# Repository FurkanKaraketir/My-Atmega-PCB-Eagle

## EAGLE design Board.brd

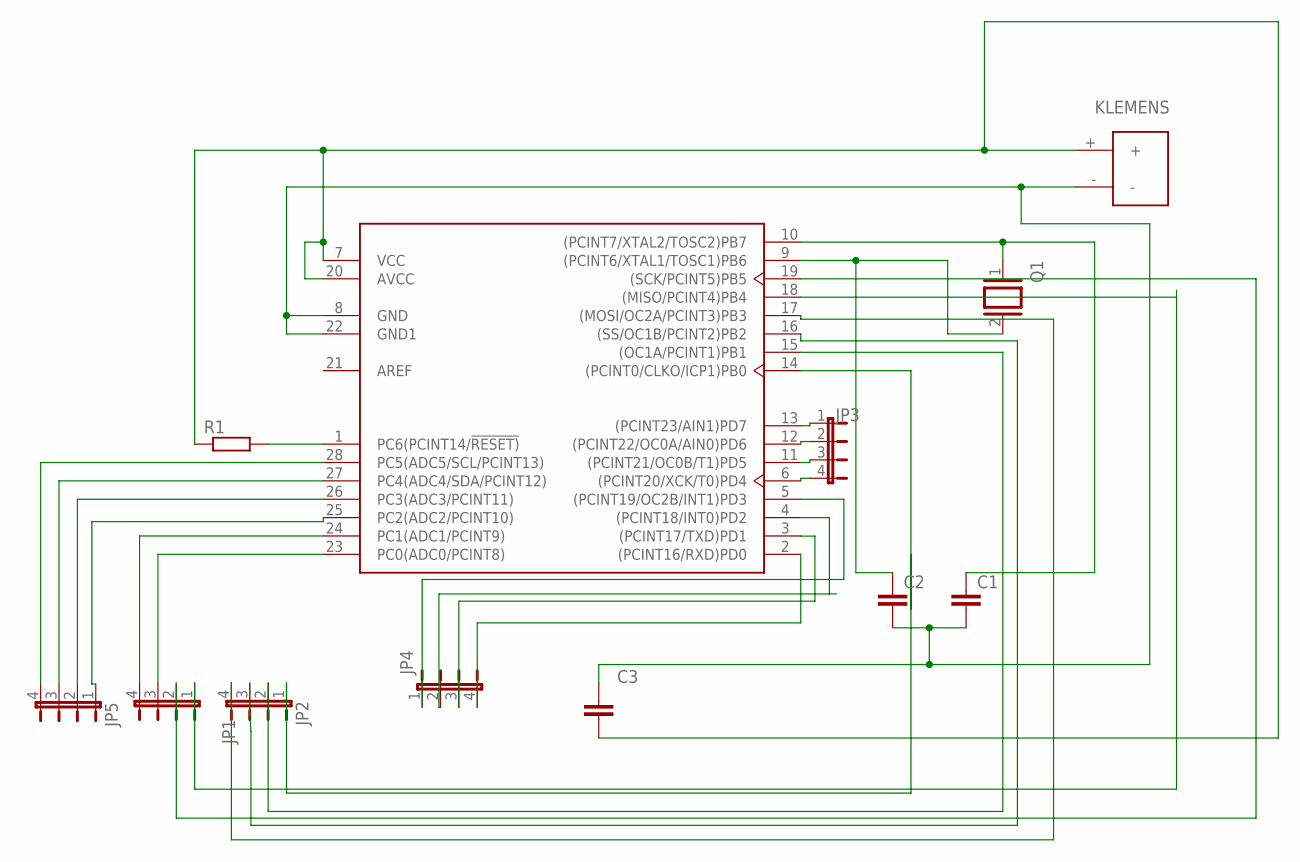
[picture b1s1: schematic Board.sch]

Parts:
C1, C2: C-EU050-025X075; C050-025X075
C3: C_RADIAL-12.5MM-DIA; CAPRD550W60D1025H1250B
JP1, JP2, JP3, JP4, JP5: JP4E; JP4
Q1: XTAL/S; QS
R1: R0207/10; 0207/10
U1: ATMEGA328P-PU; DIP-28
U$1: 2X1KLEMENS

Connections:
unnamed: C3.2, R1.1, U1.7 (VCC), U1.20 (AVCC), U$1.+
unnamed: JP4.4, U1.2 ((PCINT16/RXD)PD0)
unnamed: R1.2, U1.1 (PC6(PCINT14/!RESET))
unnamed: C1.1, Q1.1, U1.10 ((PCINT7/XTAL2/TOSC2)PB7)
unnamed: C2.1, Q1.2, U1.9 ((PCINT6/XTAL1/TOSC1)PB6)
unnamed: C1.2, C2.2, C3.1, U1.8 (GND), U1.22 (GND1), U$1.-
unnamed: JP4.2, U1.4 ((PCINT18/INT0)PD2)
unnamed: JP4.3, U1.3 ((PCINT17/TXD)PD1)
unnamed: JP3.1, U1.13 ((PCINT23/AIN1)PD7)
unnamed: JP3.2, U1.12 ((PCINT22/OC0A/AIN0)PD6)
unnamed: JP3.3, U1.11 ((PCINT21/OC0B/T1)PD5)
unnamed: JP2.1, U1.14 ((PCINT0/CLKO/ICP1)PB0)
unnamed: JP2.2, U1.15 ((OC1A/PCINT1)PB1)
unnamed: JP2.3, U1.16 ((SS/OC1B/PCINT2)PB2)
unnamed: JP2.4, U1.17 ((MOSI/OC2A/PCINT3)PB3)
unnamed: JP1.1, U1.18 ((MISO/PCINT4)PB4)
unnamed: JP1.2, U1.19 ((SCK/PCINT5)PB5)
unnamed: JP1.3, U1.23 (PC0(ADC0/PCINT8))
unnamed: JP1.4, U1.24 (PC1(ADC1/PCINT9))
unnamed: JP5.2, U1.26 (PC3(ADC3/PCINT11))
unnamed: JP5.3, U1.27 (PC4(ADC4/SDA/PCINT12))
unnamed: JP5.4, U1.28 (PC5(ADC5/SCL/PCINT13))
unnamed: JP4.1, U1.5 ((PCINT19/OC2B/INT1)PD3)
unnamed: JP5.1, U1.25 (PC2(ADC2/PCINT10))
unnamed: JP3.4, U1.6 ((PCINT20/XCK/T0)PD4)

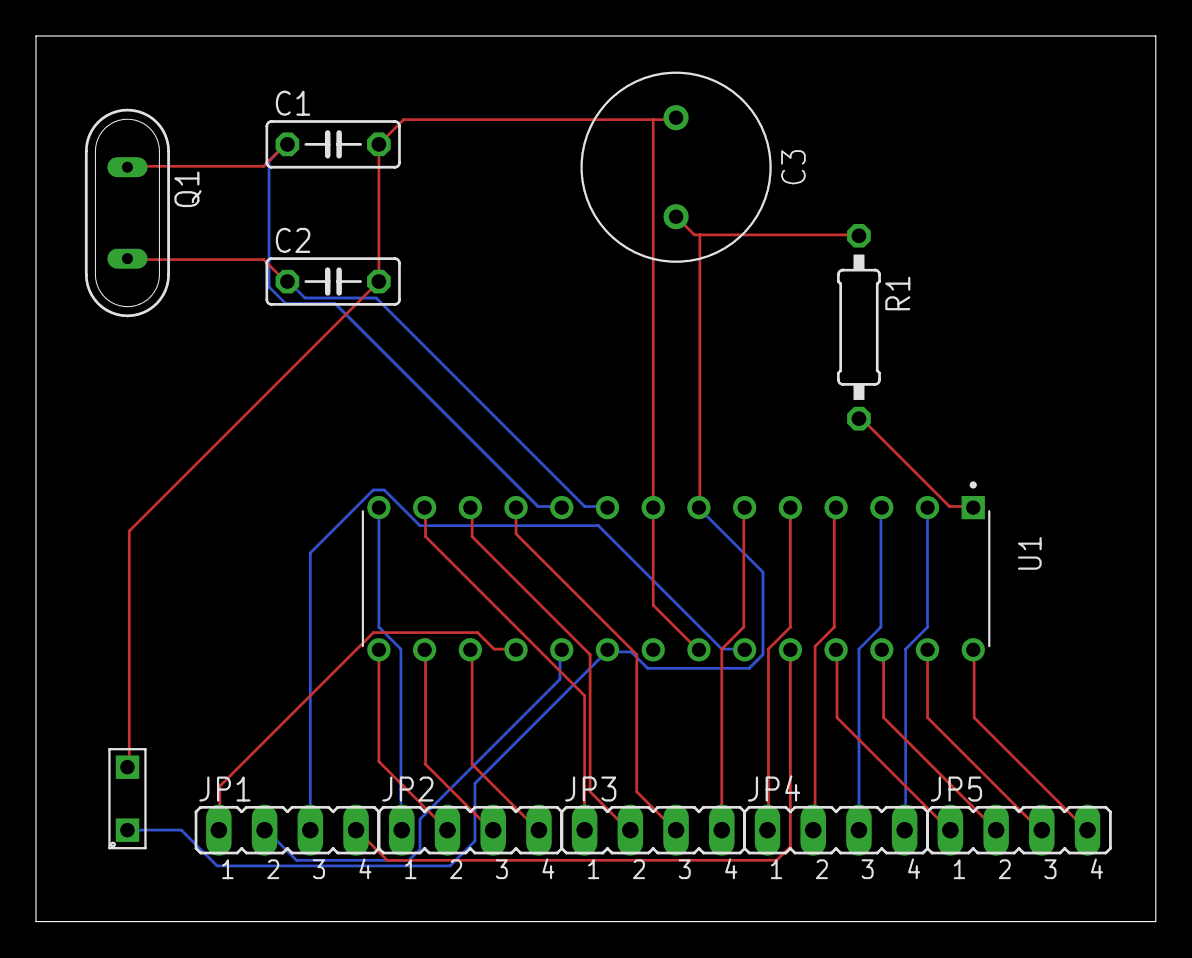
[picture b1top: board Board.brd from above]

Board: 2 copper layers, 62.2 x 49.2 mm, 12 parts (0 on the bottom side), 25 nets.
